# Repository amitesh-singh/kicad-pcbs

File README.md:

### links

sabor awesome shift register boards
* http://repos.borg.ch/projects/pcbs/trunk/shift_regs/doc/shift_regs.sch.svg
* http://repos.borg.ch/projects/pcbs/trunk/shift_regs/doc/shift_regs_bidi.sch.svg
* http://repos.borg.ch/projects/pcbs/trunk/shift_regs/doc/shift_regs_bidi.html

### manifacturer
- oshpark: 6 dollars per 3 board (5cm x 5cm) - prototype service  
   http://docs.oshpark.com/services/
   * i probably order my first board from here.
- https://www.elecrow.com/services/pcb-prototyping.html
-  macrofab https://macrofab.com/
- seedstudio
- dirtypcb : dirtypcb wants *edge.cuts.gm1 into *.gko extension
- lionscircuits: http://www.lioncircuits.com/ -  looks promising for small number for prototypes.

### Enable menu icons
On my home PC, the menu icons were absent in kicad somehow.
running this command fixes those:

$ gsettings set org.gnome.settings-daemon.plugins.xsettings overrides "{'Gtk/ButtonImages': <1>, 'Gtk/MenuImages': <1>}"

### Panelize PCBs
- http://projects.borg.ch/electronics/kicad/panelize.html#A%20Bigger%20Example

- put 2.5-3mm space between each pcb as 1mm space would take up by cutter tool.
#### how to use panelize script
 panelize.py configfile
### Custom PCBs how to
 https://andrehessling.de/2016/09/13/getting-a-custom-board-outline-from-an-svg-file-into-kicad/

### lib and pretty file for ICs
 - https://www.snapeda.com/about/import/

### Kicad setup guide

#### first time setup.  

1. Setting folders for lib,footprints and 3d shapes.

- create a dir named "Kicad" in ~/repos/
- cd Kicad
- git clone https://github.com/KiCad/kicad-library
- git clone https://github.com/KiCad/kicad-packages3D
- git clone https://github.com/KiCad/kicad-footprints
- open Kicad  
   Go to Preferences -> Configure path ->  
   KICAD_PTEMPLATES -> /home/ami/repos/KiCad/kicad-library/template    
   KIGITHUB -> https://github.com/KiCad  
   KISYS3DMOD -> /home/ami/repos/KiCad/kicad-packages3D  
   KISYSMOD -> /home/ami/repos/KiCad/kicad-library/modules  
- open any sch file and do following things  
  Preferences -> component libraries  
  delete all components library files
  click add -> go to /home/ami/repos/KiCad/kicad-library/library and selet all .lib files.  

- open any kicad_pcb files and Preferences -> Footprint libraries manager & delete all the libraries  
  click append with Wizard -> Files on computer -> Next -> /home/ami/repos/KiCad/kicad-footprints and select all the folders

#### setting traces size

PCBNew -> Design rules -> Global design tab

Add track1 - 0.1524  
    track2 - 0.254   
    track3 - 0.381  
    track4 - 0.508
    track5 - 0.8128

    For digital circuits 5v/3.3v, we generally use Track width size 0.381mm

Adding generic Net classes for Power  
Click-> Add -> New Net Class Name -> Power ->  
Clerance -> 0.25  
Track Width -> 0.38  
Via Dia -> 0.4  
Via Drill -> 0.3  
uVia Dia -> 0.3  
uVia Drill -> 0.1  

Go on left side and select Vcc/5v/3.3v/GND and let them use Power Net Class.

Generate good looking PCB artwork from KiCAD 
- https://onetransistor.blogspot.kr/2017/04/kicad-pcb-artwork-display.html?m=1

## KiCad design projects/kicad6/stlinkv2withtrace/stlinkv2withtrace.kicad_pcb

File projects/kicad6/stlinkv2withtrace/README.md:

# make bluepill as stlink

- made this kicad design and it works well 
- refer to this guide 
- https://slemi.info/2018/08/14/making-your-own-st-link-v2/
- https://github.com/skeyzero/stlink_V2/
- already downloaded the hex file in the current folder
On linux,

```
sudo apt install stlink-tools
st-flash --reset --format ihex stlink.hex

```

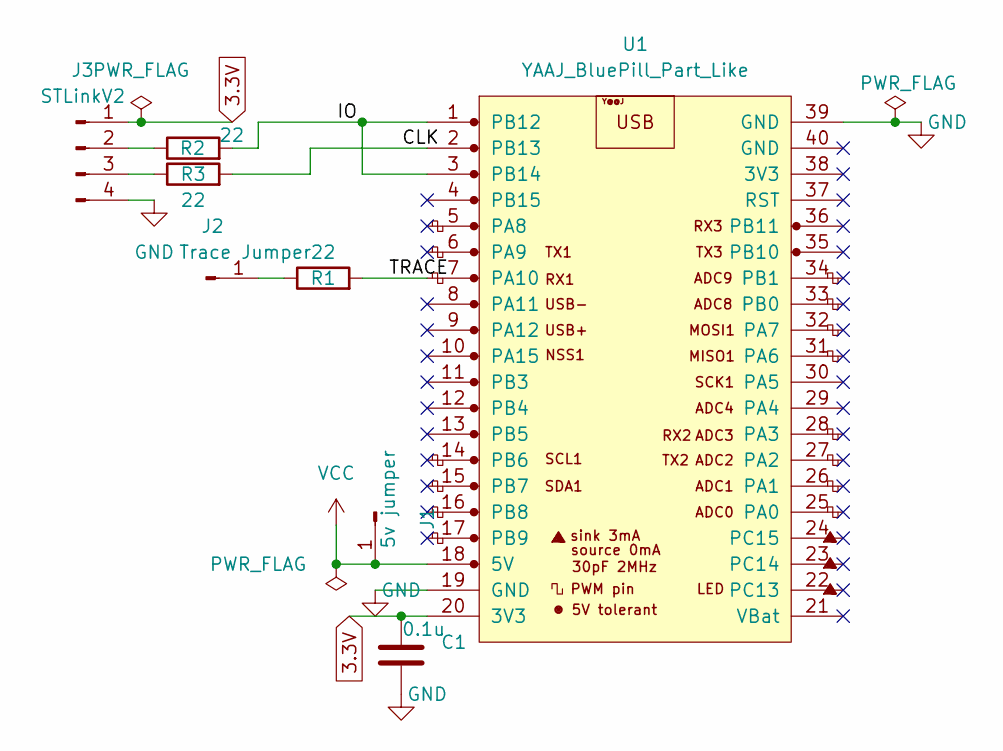
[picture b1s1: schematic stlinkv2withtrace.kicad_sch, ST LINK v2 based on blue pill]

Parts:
C1: 0.1u; C_Axial_L3.8mm_D2.6mm_P7.50mm_Horizontal
J1: 5v jumper; PinSocket_1x01_P2.54mm_Vertical
J2: Trace Jumper; PinSocket_1x01_P2.54mm_Vertical
J3: STLinkV2; PinSocket_1x04_P2.54mm_Horizontal
R1, R2, R3: 22; R_Axial_DIN0207_L6.3mm_D2.5mm_P7.62mm_Horizontal
U1: YAAJ_BluePill_Part_Like; YAAJ_BluePill_2

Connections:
3.3V: C1.1, J3.1, U1.20 (3V3)
/CLK: R3.2, U1.2 (PB13)
/IO: R2.2, U1.1 (PB12), U1.3 (PB14)
/TRACE: R1.2, U1.7 (PA10)
GND: C1.2, J3.4, U1.19 (GND), U1.39 (GND)
unnamed: J2.1, R1.1
unnamed: J3.2, R2.1
unnamed: J3.3, R3.1
VCC: J1.1, U1.18 (5V)

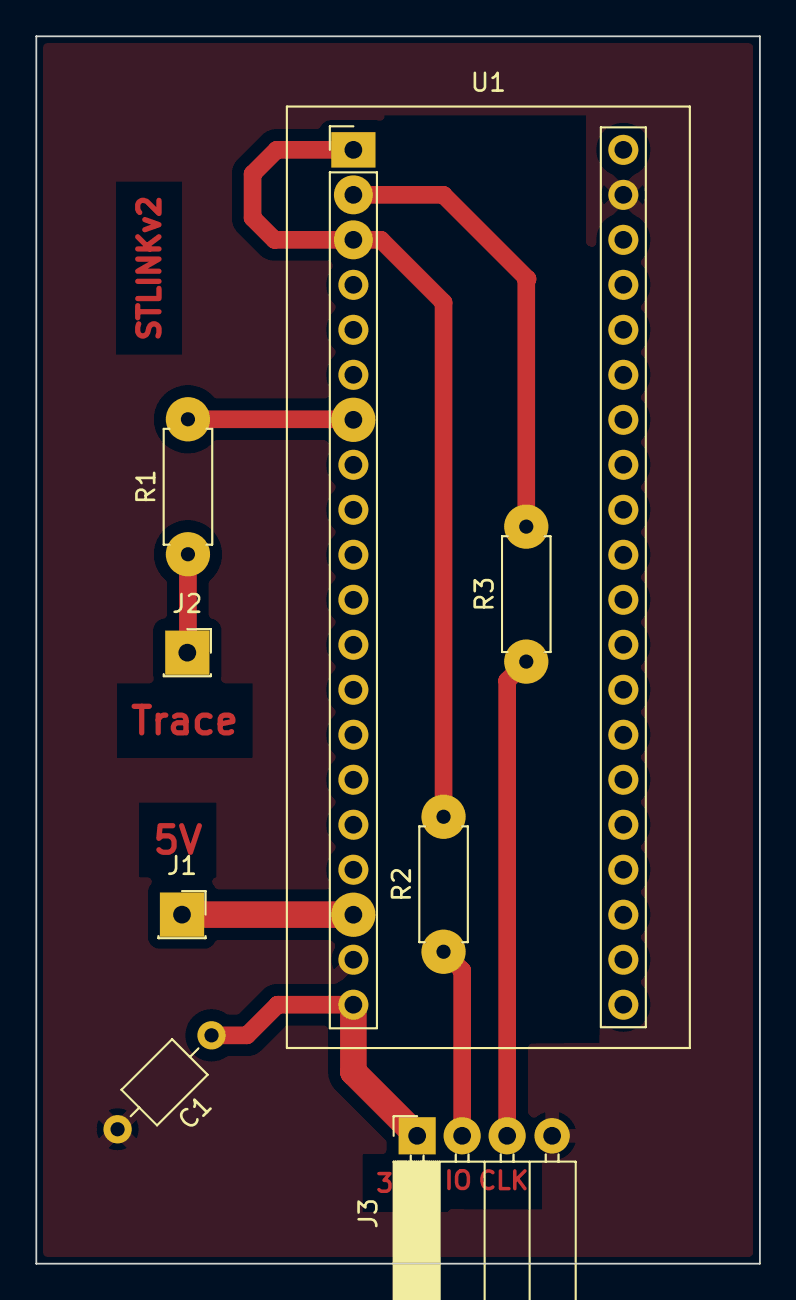
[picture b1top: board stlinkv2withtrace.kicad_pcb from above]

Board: 2 copper layers, 40.9 x 69.3 mm, 8 parts (0 on the bottom side), 9 nets.

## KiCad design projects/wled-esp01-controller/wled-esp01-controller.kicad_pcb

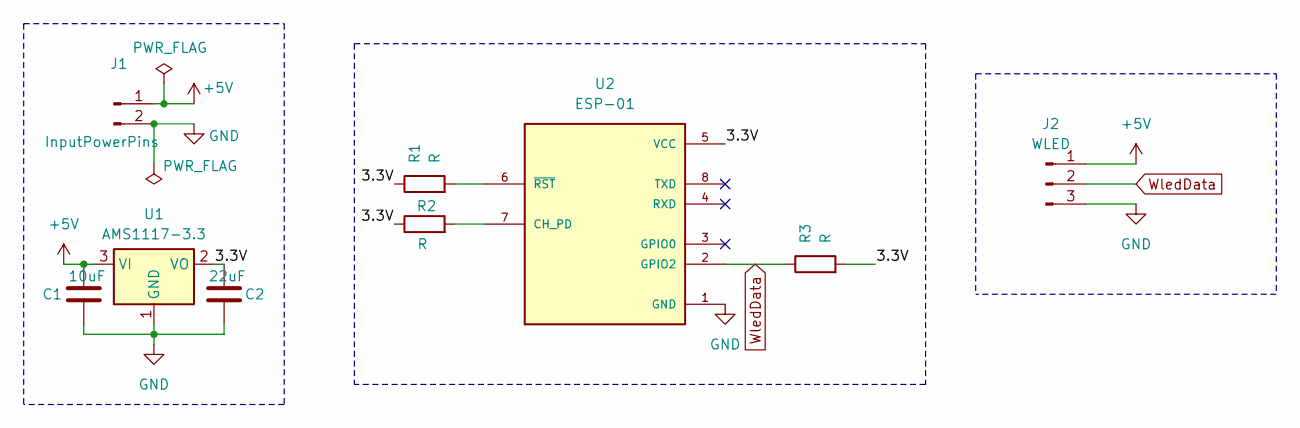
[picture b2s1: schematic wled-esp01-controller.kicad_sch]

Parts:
C1: 10uF; C_Rect_L4.0mm_W2.5mm_P2.50mm
C2: 22uF; C_Rect_L4.0mm_W2.5mm_P2.50mm
J1: InputPowerPins; PinHeader_1x02_P2.54mm_Vertical
J2: WLED; PinHeader_1x03_P2.54mm_Vertical
R1, R2, R3: R; R_0805_2012Metric_Pad1.20x1.40mm_HandSolder
U1: AMS1117-3.3; SOT-223-3_TabPin2
U2: ESP-01; MODULE_ESP-01; PARTREV 1.0

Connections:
+5V: C1.1, J1.1, J2.1, U1.3 (VI)
/3.3V: C2.1, R1.1, R2.1, R3.2, U1.2 (VO), U2.5 (VCC)
GND: C1.2, C2.2, J1.2, J2.3, U1.1 (GND), U2.1 (GND)
unnamed: R2.2, U2.7 (CH_PD)
unnamed: R1.2, U2.6 (~RST)
WledData: J2.2, R3.1, U2.2 (GPIO2)

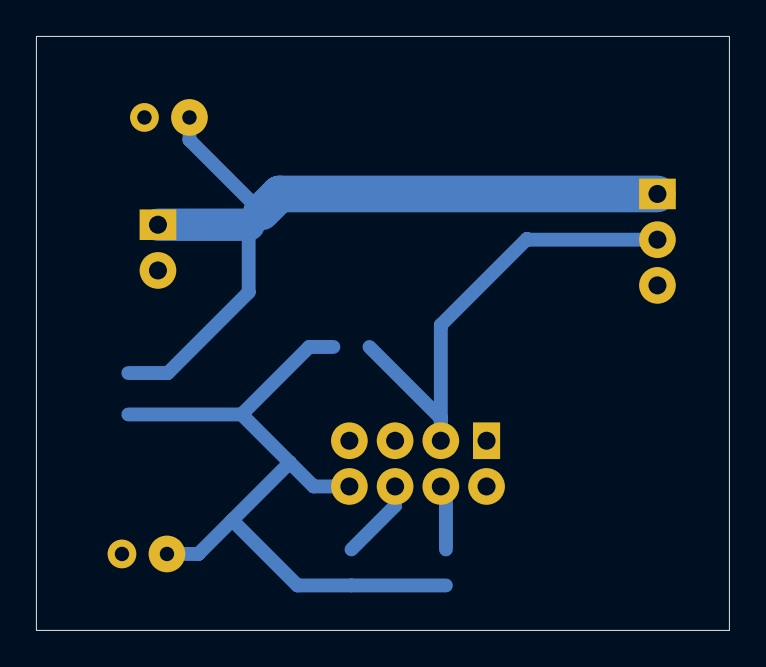
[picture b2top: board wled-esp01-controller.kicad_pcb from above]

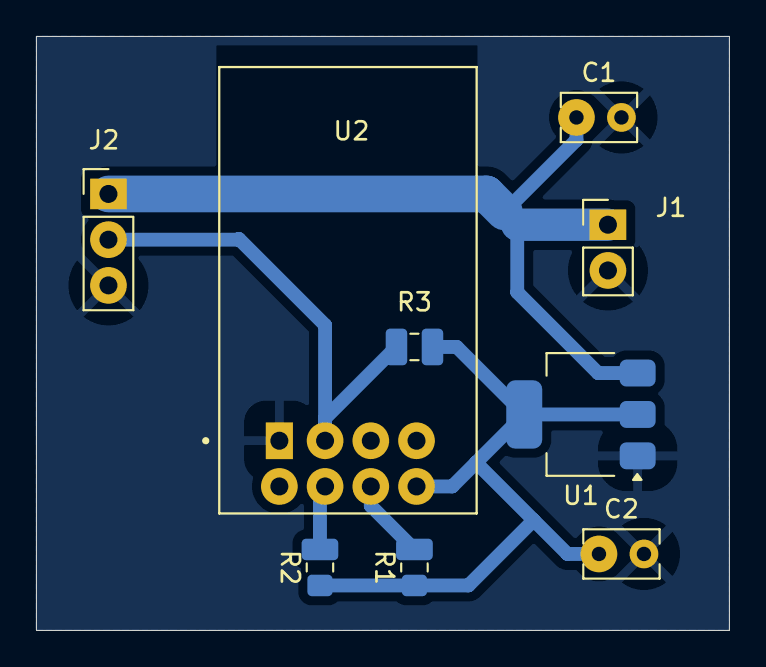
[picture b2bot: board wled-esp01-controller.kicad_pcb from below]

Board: 2 copper layers, 38.5 x 33.0 mm, 9 parts (9 on the bottom side), 6 nets.

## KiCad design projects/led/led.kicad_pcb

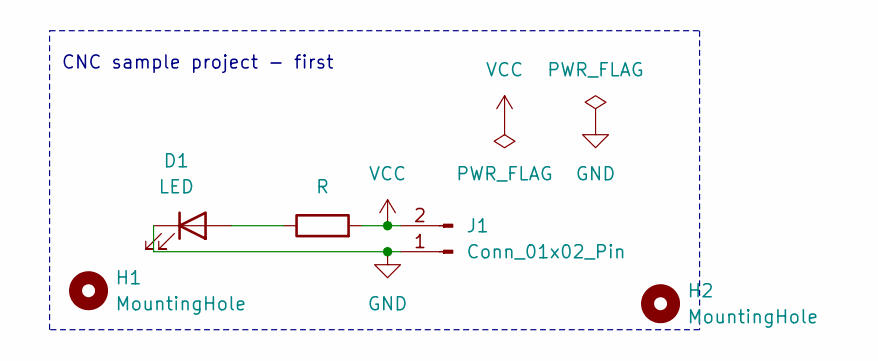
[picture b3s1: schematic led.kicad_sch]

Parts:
D1: LED; LED_0805_2012Metric
H1, H2: MountingHole; MountingHole_2.2mm_M2_DIN965
J1: Conn_01x02_Pin; JST_EH_B2B-EH-A_1x02_P2.50mm_Vertical
R1: R; LED_0805_2012Metric

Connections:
GND: D1.1 (K), J1.1
unnamed: D1.2 (A), R1.1
VCC: J1.2, R1.2

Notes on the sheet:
CNC sample project - first

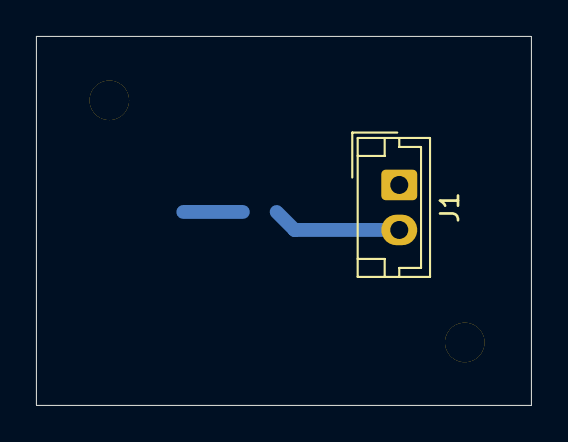
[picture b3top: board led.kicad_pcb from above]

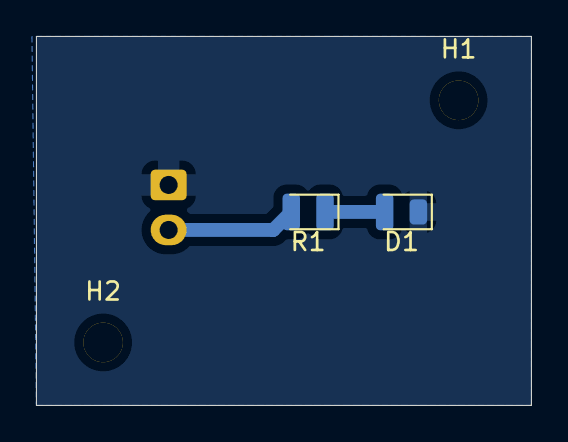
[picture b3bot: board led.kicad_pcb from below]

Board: 2 copper layers, 27.5 x 20.5 mm, 5 parts (4 on the bottom side), 3 nets.

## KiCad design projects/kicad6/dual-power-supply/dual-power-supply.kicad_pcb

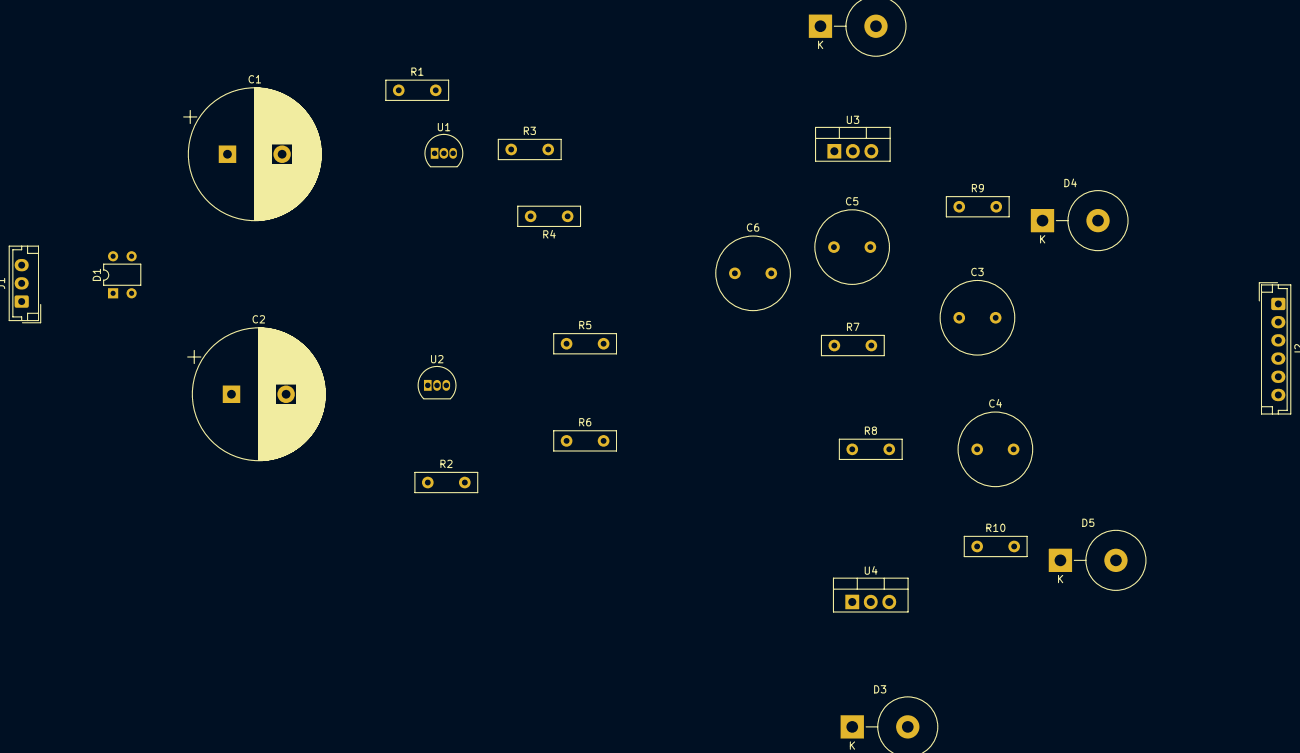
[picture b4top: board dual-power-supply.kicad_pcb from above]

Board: 2 copper layers, 27 parts (0 on the bottom side), 13 nets, no tracks yet.

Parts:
C1, C2: 1000u; CP_Radial_D18.0mm_P7.50mm
C3, C4, C5, C6: 10u; C_Radial_D10.0mm_H12.5mm_P5.00mm
D1: D_Bridge_+-AA; Diode_Bridge_DIP-4_W5.08mm_P2.54mm
D2, D3, D4, D5: D; D_5KPW_P7.62mm_Vertical_KathodeUp
J1: Conn_01x03_Male; JST_EH_B3B-EH-A_1x03_P2.50mm_Vertical
J2: Conn_01x06_Male; JST_EH_B6B-EH-A_1x06_P2.50mm_Vertical
R1, R2: 5k; R_Box_L8.4mm_W2.5mm_P5.08mm
R3, R4, R5, R6: 1k; R_Box_L8.4mm_W2.5mm_P5.08mm
R7, R8: R_Variable; R_Box_L8.4mm_W2.5mm_P5.08mm
R9, R10: R; R_Box_L8.4mm_W2.5mm_P5.08mm
U1, U2: TL431LP; TO-92_Inline
U3: LM317_TO-220; TO-220-3_Vertical
U4: LM337_TO220; TO-220-3_Vertical

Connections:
/AC1: D1.3, J1.1
/AC2: D1.4, J1.3
/V+: C5.1, D2.2 (A), D4.1 (K), J2.1, J2.2, R9.1, U3.2 (VO)
/V+1.25Ref: C4.1, R3.2, R4.1, R8.1
/V-: C6.2, D3.1 (K), D5.2 (A), J2.5, J2.6, R10.2, U4.3 (VO)
/V-1.25Ref: C3.2, R5.2, R6.1, R7.2
GND: C1.2, C2.1, C5.2, C6.1, J1.2, J2.3, J2.4, R4.2, R5.1, U1.2 (A), U2.1 (REF), U2.3 (K)
unnamed: C1.1, D1.1 (+), D2.1 (K), R1.1, U3.3 (VI)
unnamed: C2.2, D1.2 (-), D3.2 (A), R2.2, U4.2 (VI)
unnamed: C3.1, D4.2 (A), R7.1, R9.2, U3.1 (ADJ)
unnamed: C4.2, D5.1 (K), R8.2, R10.1, U4.1 (ADJ)
unnamed: R1.2, R3.1, U1.1 (REF), U1.3 (K)
unnamed: R2.1, R6.2, U2.2 (A)

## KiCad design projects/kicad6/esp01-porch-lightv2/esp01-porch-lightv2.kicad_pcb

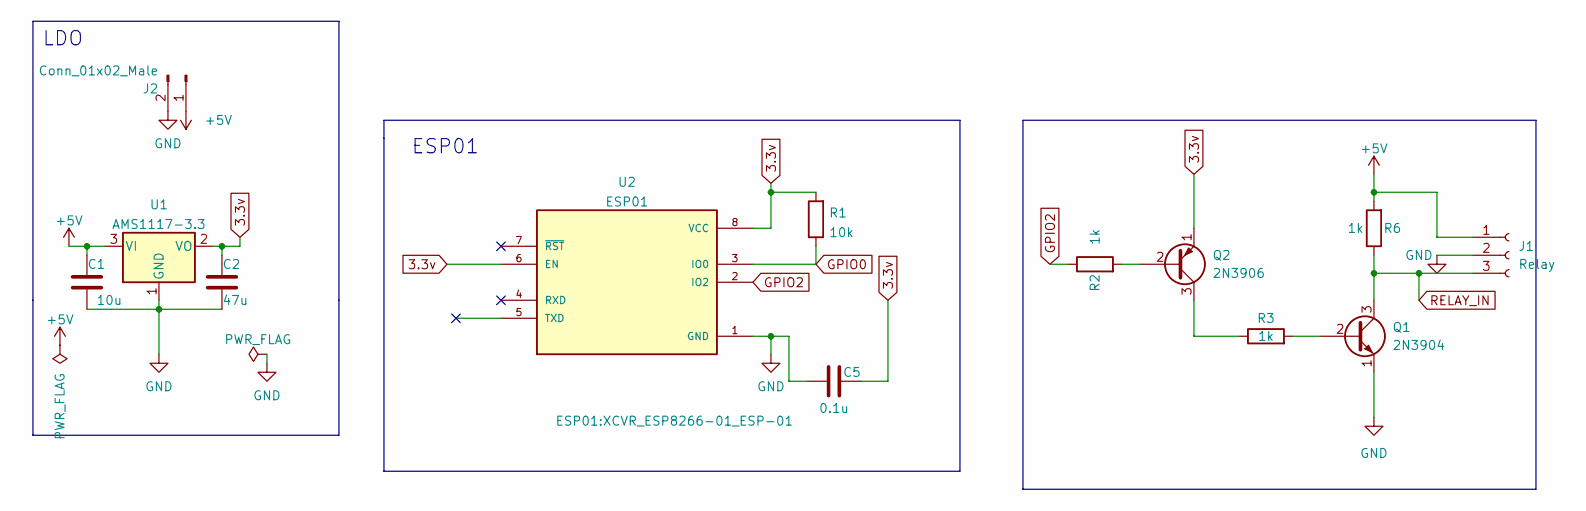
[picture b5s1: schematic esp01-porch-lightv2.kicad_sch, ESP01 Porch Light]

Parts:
C1: 10u; C_0805_2012Metric_Pad1.18x1.45mm_HandSolder
C2: 47u; C_0805_2012Metric_Pad1.18x1.45mm_HandSolder
C5: 0.1u; C_0805_2012Metric_Pad1.18x1.45mm_HandSolder
J1: Relay; PinSocket_1x03_P2.54mm_Vertical
J2: Conn_01x02_Male; PinSocket_1x02_P2.54mm_Vertical
Q1: 2N3904; TO-92_Wide
Q2: 2N3906; TO-92_Wide
R1: 10k; R_0805_2012Metric_Pad1.20x1.40mm_HandSolder
R2, R3, R6: 1k; R_0805_2012Metric_Pad1.20x1.40mm_HandSolder
U1: AMS1117-3.3; SOT-223-3_TabPin2
U2: ESP01; XCVR_ESP8266-01_ESP-01; PARTREV V1.2

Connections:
3.3v: C2.1, C5.1, Q2.1 (E), R1.2, U1.2 (VO), U2.6 (EN), U2.8 (VCC)
+5V: C1.1, J1.1, J2.1, R6.2, U1.3 (VI)
GND: C1.2, C2.2, C5.2, J1.2, J2.2, Q1.1 (E), U1.1 (GND), U2.1 (GND)
GPIO0: R1.1, U2.3 (IO0)
GPIO2: R2.1, U2.2 (IO2)
unnamed: Q1.2 (B), R3.2
unnamed: Q2.2 (B), R2.2
unnamed: Q2.3 (C), R3.1
RELAY_IN: J1.3, Q1.3 (C), R6.1

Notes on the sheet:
ESP01
LDO

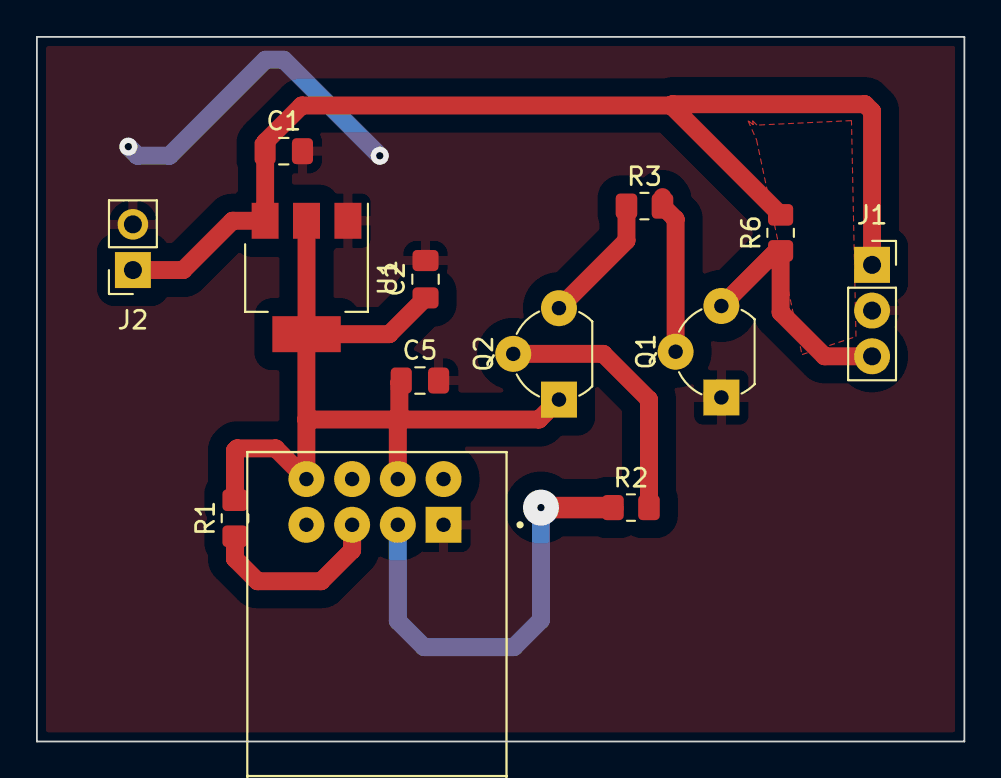
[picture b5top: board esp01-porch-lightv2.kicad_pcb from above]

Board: 2 copper layers, 51.5 x 39.1 mm, 13 parts (0 on the bottom side), 9 nets.

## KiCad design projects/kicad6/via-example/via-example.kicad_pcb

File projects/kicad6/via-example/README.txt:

Use this via example for making jumper wire enabled
single layer board for etching at home.

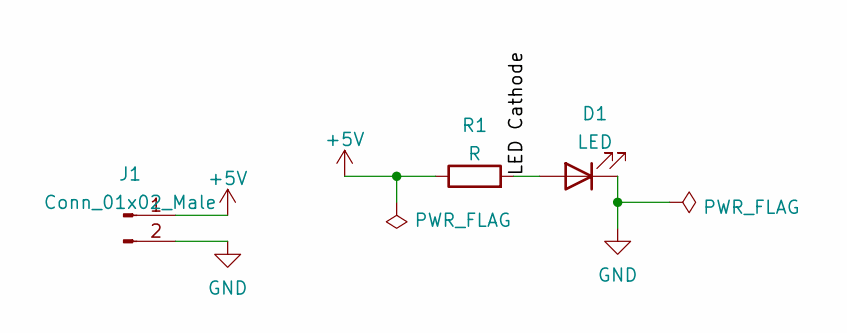
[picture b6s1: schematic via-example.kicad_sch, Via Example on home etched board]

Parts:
D1: LED; LED_0805_2012Metric_Pad1.15x1.40mm_HandSolder
J1: Conn_01x02_Male; PinSocket_1x02_P2.54mm_Vertical
R1: R; R_0805_2012Metric_Pad1.20x1.40mm_HandSolder

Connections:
+5V: J1.1, R1.1
/LED Cathode: D1.2 (A), R1.2
GND: D1.1 (K), J1.2

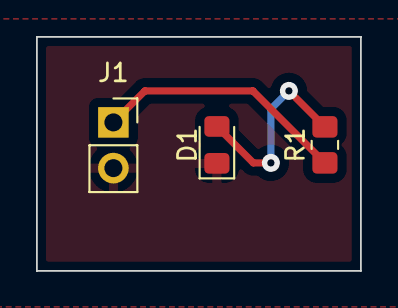
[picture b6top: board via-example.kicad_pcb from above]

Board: 2 copper layers, 18.0 x 13.0 mm, 3 parts (0 on the bottom side), 3 nets.

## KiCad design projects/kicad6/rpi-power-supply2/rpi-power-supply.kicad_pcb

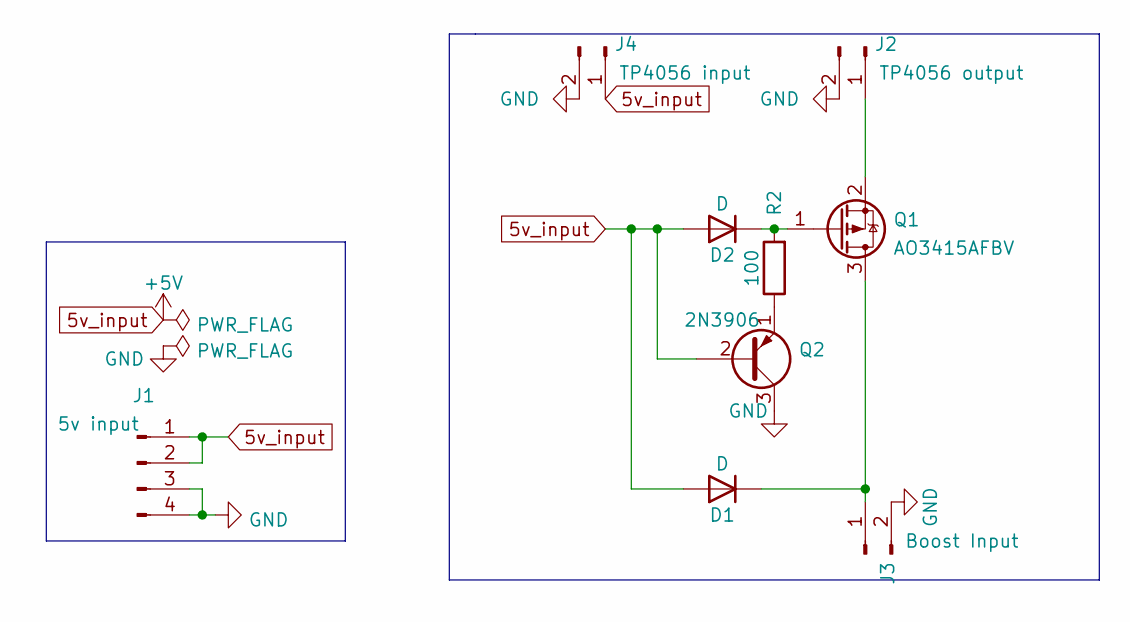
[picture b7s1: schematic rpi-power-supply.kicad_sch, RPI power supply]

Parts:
D1, D2: D; D_3220_8050Metric_Pad2.65x5.15mm_HandSolder
J1: 5v input; PinHeader_1x04_P2.54mm_Vertical_ETCH
J2: TP4056 output; PinSocket_1x02_P2.54mm_Vertical_ETCH
J3: Boost Input; PinSocket_1x02_P2.54mm_Vertical_ETCH
J4: TP4056 input; PinSocket_1x02_P2.54mm_Vertical_ETCH
Q1: AO3415AFBV; SOT-23_Handsoldering
Q2: 2N3906; TO-92_HandSolder
R2: 100; R_0805_2012Metric_Pad1.20x1.40mm_HandSolder

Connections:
5v_input: D1.2 (A), D2.2 (A), J1.1, J1.2, J4.1, Q2.2 (B)
GND: J1.3, J1.4, J2.2, J3.2, J4.2, Q2.3 (C)
unnamed: D2.1 (K), Q1.1 (G), R2.2
unnamed: J2.1, Q1.2 (S)
unnamed: D1.1 (K), J3.1, Q1.3 (D)
unnamed: Q2.1 (E), R2.1

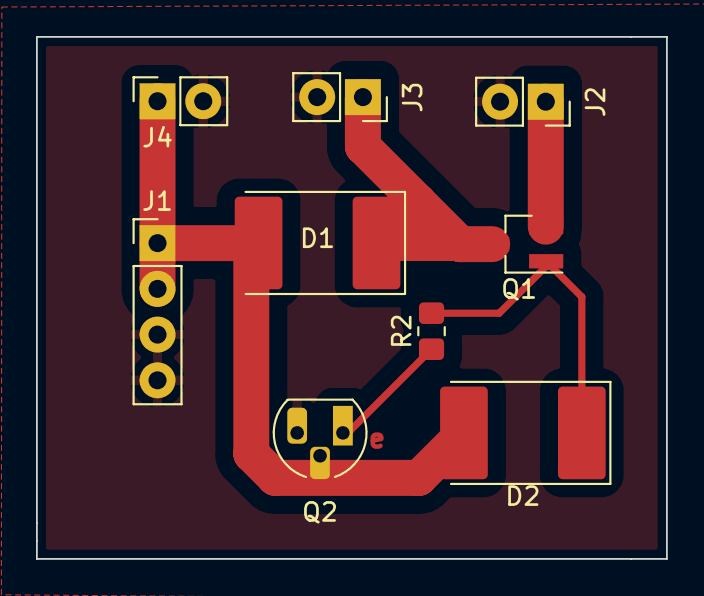
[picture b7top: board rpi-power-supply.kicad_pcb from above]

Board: 2 copper layers, 35.0 x 29.0 mm, 9 parts (0 on the bottom side), 6 nets.

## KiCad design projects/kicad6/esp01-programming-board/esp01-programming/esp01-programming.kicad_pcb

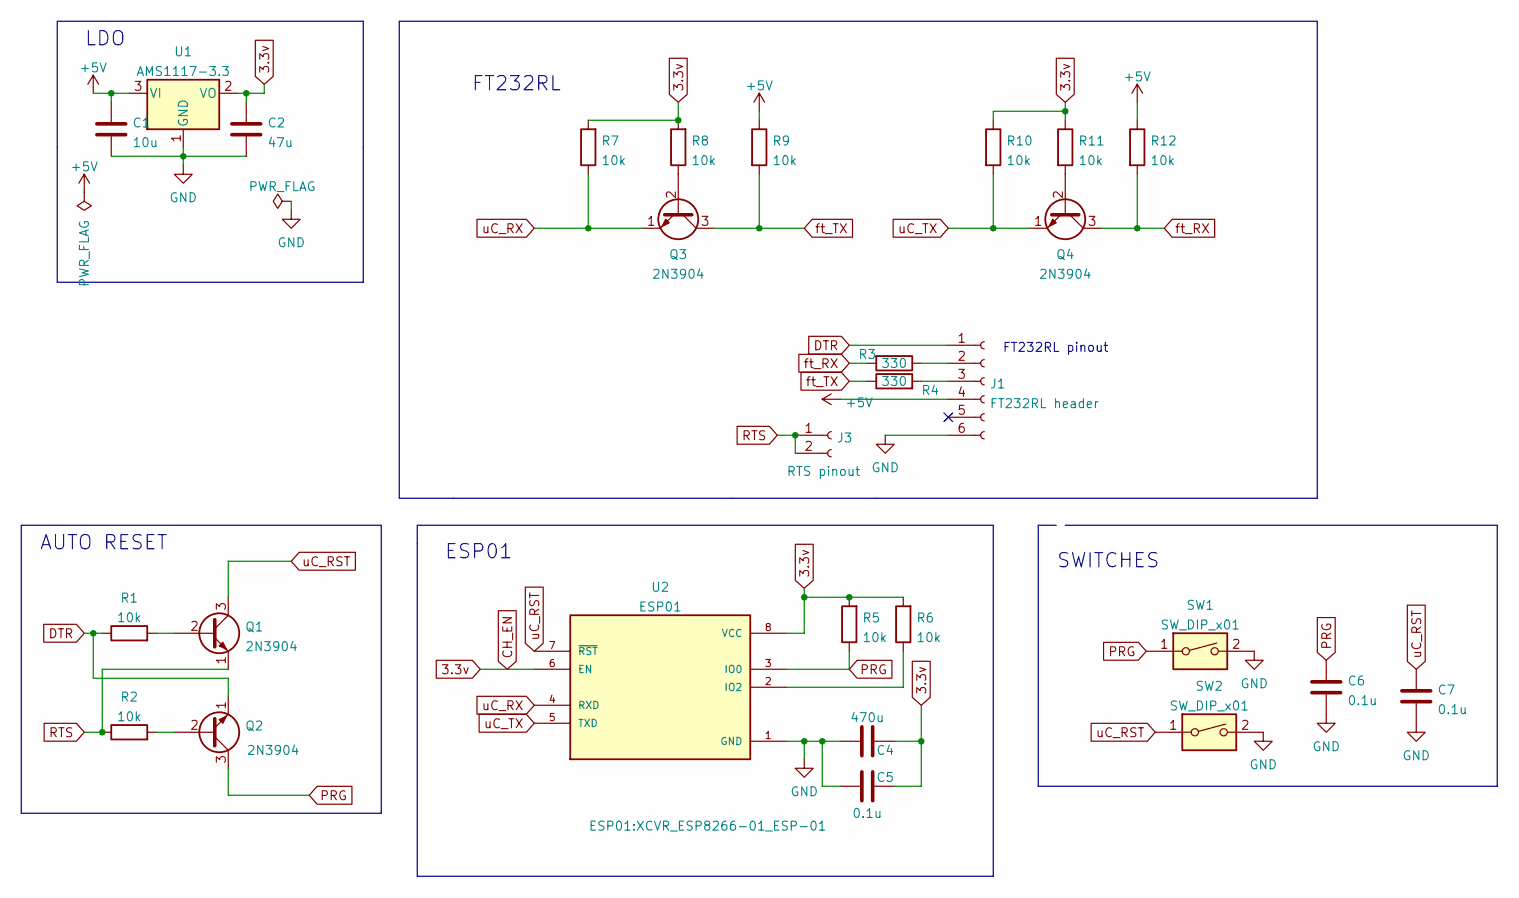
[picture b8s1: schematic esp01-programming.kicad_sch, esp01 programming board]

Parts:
C1: 10u; C_0805_2012Metric_Pad1.18x1.45mm_HandSolder
C2: 47u; C_0805_2012Metric_Pad1.18x1.45mm_HandSolder
C4: 470u; C_Radial_D4.0mm_H7.0mm_P1.50mm
C5, C6, C7: 0.1u; C_0805_2012Metric_Pad1.18x1.45mm_HandSolder
J1: FT232RL header; PinHeader_1x06_P2.54mm_Vertical
J3: RTS pinout; PinSocket_1x02_P2.54mm_Vertical_ETCH
Q1, Q2, Q3, Q4: 2N3904; TO-92_Wide
R1, R2, R5, R6, R7, R8, R9, R10, R11, R12: 10k; R_0805_2012Metric_Pad1.20x1.40mm_HandSolder
R3, R4: 330; R_0805_2012Metric_Pad1.20x1.40mm_HandSolder
SW1, SW2: SW_DIP_x01; SW_PUSH_6mm_H5mm
U1: AMS1117-3.3; SOT-223-3_TabPin2
U2: ESP01; XCVR_ESP8266-01_ESP-01; PARTREV V1.2

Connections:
3.3v: C2.1, C4.1, C5.1, R5.2, R6.2, R7.2, R8.2, R10.1, R11.1, U1.2 (VO), U2.6 (EN), U2.8 (VCC)
+5V: C1.1, J1.4, R9.1, R12.1, U1.3 (VI)
DTR: J1.1, Q2.1 (E), R1.1
GND: C1.2, C2.2, C4.2, C5.2, C6.2, C7.1, J1.6, SW1.2, SW2.2, U1.1 (GND), U2.1 (GND)
unnamed: J1.2, R3.1
unnamed: J1.3, R4.2
unnamed: Q1.2 (B), R1.2
unnamed: Q2.2 (B), R2.2
unnamed: Q3.2 (B), R8.1
unnamed: Q4.2 (B), R11.2
unnamed: R6.1, U2.2 (IO2)
PRG: C6.1, Q2.3 (C), R5.1, SW1.1, U2.3 (IO0)
RTS: J3.1, J3.2, Q1.1 (E), R2.1
ft_RX: Q4.3 (C), R3.2, R12.2
ft_TX: Q3.3 (C), R4.1, R9.2
uC_RST: C7.2, Q1.3 (C), SW2.1, U2.7 (~RST)
uC_RX: Q3.1 (E), R7.1, U2.4 (RXD)
uC_TX: Q4.1 (E), R10.2, U2.5 (TXD)

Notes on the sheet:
SWITCHES
LDO
ESP01
FT232RL
AUTO RESET
FT232RL pinout

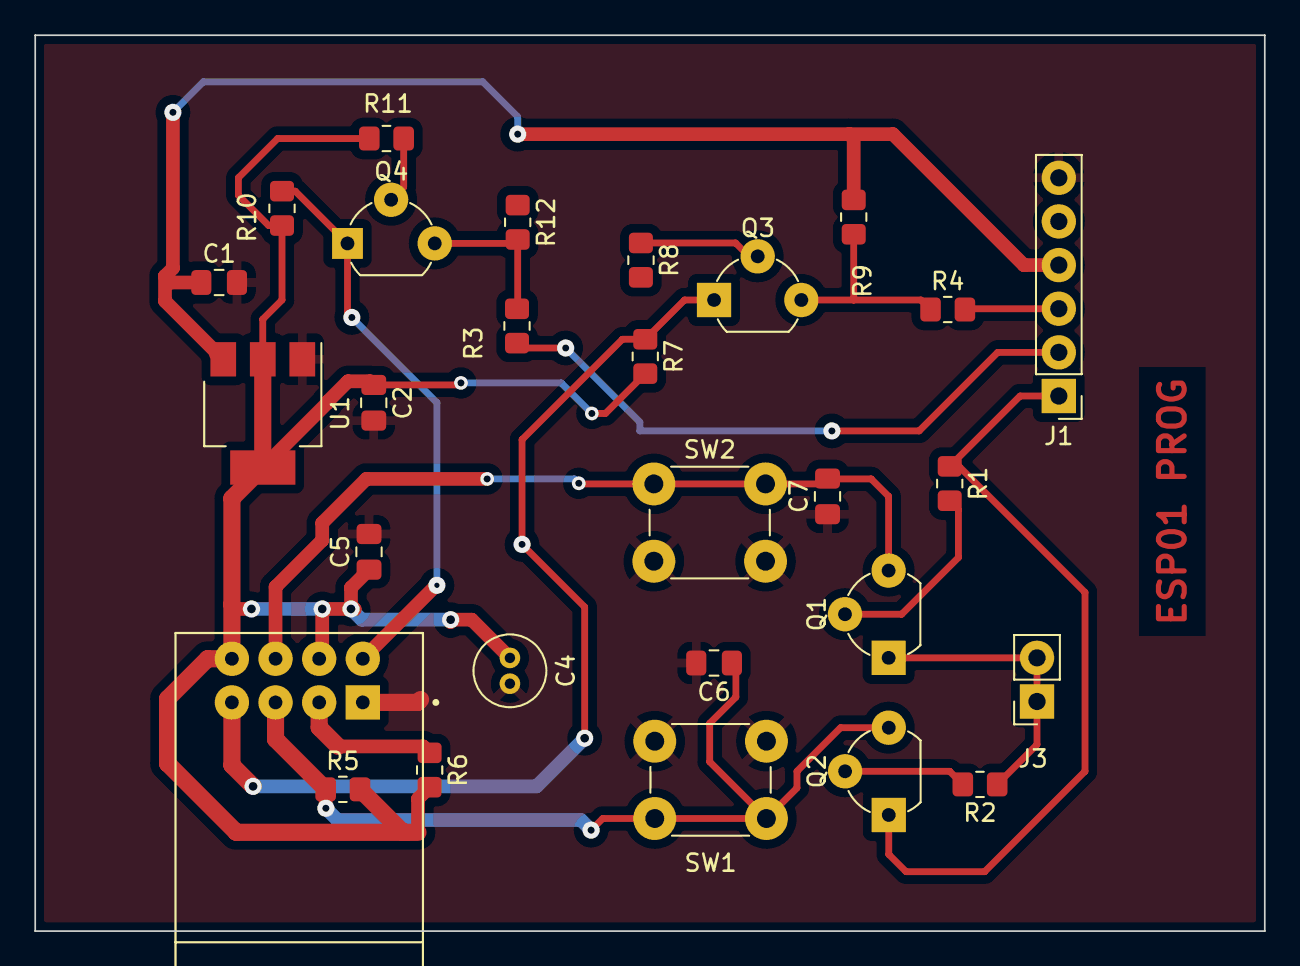
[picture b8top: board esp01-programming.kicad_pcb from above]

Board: 2 copper layers, 71.6 x 52.1 mm, 28 parts (0 on the bottom side), 18 nets.

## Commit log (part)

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2016-09-04 Add atmega16 schematics and fritzing file.
2016-09-10 Add new parts
2016-10-02 led sketch added
2016-10-12 Add new designs
2016-10-23 Add led example for kicad.
2016-10-29 Add ST7735 breakout TFT display
2016-10-29 Add ST7735 connections with AVR atmega16a
2017-01-18 Add README
2017-01-23 Add 74hc595 sch with attiny85
2017-01-26 Add nRF24 breakout board
2017-01-26 Add nRF24 v0.2
2017-01-26 Add final nRF24 board - production ready
2017-01-27 add 7 segment schematic
2017-01-28 Add led2layer example
    - a minimal example which shows how to make
    2 layer PCB. also shows how to place a component on
    back side of pcb.
    - added a cool logo of mine on that board.
2017-01-28 Add info abt manufacturers
2017-01-28 Add a nice logo
2017-01-28 Add attiny13a schematic
2017-01-29 Add sabor panelize tool.
2017-01-29 Add new led pro
2017-01-29 Add atiny13 full schematic/pcb
2017-01-29 make a better pcb
    included sabor suggestions
    1. Change vcc copper fill to GND fill
    2. remove gnd traces
    3. redraw vcc traces
    4. move bypass capacitor close to Vcc/GND as much as possible.
2017-01-29 remove bak files
    remove backup files
2017-01-29 Add gitignore
    Add bak files
2017-01-29 change name to ISP
2017-01-29 make vcc track size bigger
2017-01-29 make vcc track size bigger
    and also add logo of board.
2017-01-29 Add sabor common libraries
2017-01-29 Add attony13a
2017-01-29 Add capacitor across switch
2017-01-29 Add 6mm switch button
2017-01-29 Add attiny13a
2017-01-29 move the headers a bit
2017-01-29 Add production ready code
2017-02-01 use latest panelize script by sabor
2017-02-01 Add panilized kicad pcb and config file
    usage:
    panelize.py config file
2017-02-01 remove gerber files
2017-02-01 make it better.
2017-02-01 Add round shape board example
2017-02-01 Add config file for panelize.
    it seems that panelize won;t work with round leds.
2017-02-02 update the 7segment a bit
    mistakes corrected.
    - remove right angled traces
    - minimize the vias
    - add a 2.0 mm hole
2017-02-02 round leds: Add one more GND plane
2017-02-02 Add Kitchen timer schematic
    add sabor digital library as well.
2017-02-02 Associate components
2017-02-02 fix the switch circuit.
2017-02-02 fix circuit for 7 segment display.
2017-11-05 make it compatible with kicad recent version
2017-11-09 kicad: add new schematic/pcb for ams1117 3.3v
2017-11-09 kicad: breadboad - add generic board skeleton
    Work in progress.
2017-11-10 breadboard: Add esp12e into board
2017-11-10 AMS1117: Add way to thermal vias
    This is based on https://www.youtube.com/watch?v=Hp5ngKtl7S4
2017-11-10 multisheet: Add multisheet example in kicad.
    This makes design look good.
2017-11-10 remove old projects
2017-11-12 breadboard: Add bboard-3rows component
2017-11-12 breadboard: make the pins type to passive.
2017-11-12 breadboard: esp12e - work is almost completed.
2017-11-12 Add gitignore
2017-11-12 Revert "Add gitignore"
    This reverts commit 1d0808174f2c1fbc4e2cf73c68065f4eadfb9096.
2017-11-12 fix sch
2017-11-13 library: Add AMS1117-3.3 lib
2017-11-13 breadboard: modify the libraries path
2017-11-13 update README.md
    Add on how to setup kicad for first time.
2017-11-13 Add latest
2017-11-13 README.md - add abt how to add track width options
2017-11-13 breadboard: add net class power
2017-11-14 breadboard: fix the mistakes in esp12e board design
2017-11-14 multisheet: Add stm32 sch imported from another project.
2017-11-14 Add multipower schematic.
2017-11-14 gitignore update
2017-11-15 Add docs abt heirarchical sheet
2020-09-28 rename the folder.
2020-10-16 update the panelize tool
2022-02-19 Add esp01 board - not finished
2022-02-28 Add rpi power supply schematic.
2022-03-04 Add via example for home etched boards
2022-03-05 Add local footprints and symbols
2022-03-12 Add esp01 porch light pcb
2022-03-12 Add esp01 adapter pcb
2022-03-12 Add MIC5209 symbol/footprint
2022-03-12 Add new changes
2022-03-12 Add new footprints
2022-03-14 esp01_porch light: fix the GNDing
2022-03-15 Add porch light updated schematic
2022-03-19 add v2 of porch light
2022-03-19 update esp 01 port light PCB
2022-03-19 esp porch ligh v2: finished
2022-04-15 Add dual power supply kicad
2022-05-08 Add doorsensor v2 version with reed switch
2022-05-15 Add stlinkv2
2022-05-17 Add stlink v2 diy programmer
2023-12-22 Add pin header 1x10 etch friendly
2023-12-31 Add new files
2023-12-31 freecad/learning sample: add a sample
2024-01-01 freecad readme
2024-01-03 Add more freecad designs
2024-01-03 Add Gear readme
2024-01-03 freecad: trim edge example
2024-01-03 freecad: Add gear and mirror examples
2024-01-04 freecad: Add text example
2024-01-06 Add more freeCad projects
2024-01-07 freeCAD: add angled hole example
2024-01-07 freeCad: add cool projects
2024-01-15 freeCAD: add car mobile holder leg
    This fixes my car mobile holder
2024-01-15 freecad: Add glass
2024-01-16 animation example
2024-01-16 add more animation
2024-01-25 add new code
2024-01-26 Add more files
2024-01-29 Add more
2024-01-29 freeCAD: final project
2024-02-01 Add best design for making box
2024-02-01 Add reamde
2024-02-03 freeCAD: add new projects
2024-02-04 Add PCB shaker project desc
2024-02-04 Adafruit design - reverse engineering
2024-02-05 Add boolean op example
2024-02-06 freeCAD: add extension drawing
2024-02-07 freeCAD: add new designs
2024-02-08 freeCAD: add more projects
2024-02-09 Add printerRefillBottle Cap example
2024-02-11 Add config table example
2024-02-23 freecad: Add springs example
2024-03-05 Add spoon
2024-03-28 Add snap-fit example
2024-04-03 add snap-fit box example
2024-04-21 Add usb boost power supply
    XY-016 2A DC-DC Step Up 5V/9V/12V/28V Power Module with Micro USB
2024-04-26 add thickness example
2024-11-29 freecad: add dice example
2024-11-30 Add updated one
2024-12-31 Add jumper wire organizer
2025-01-31 Add latest freecad stuffs
2025-01-31 add door stopper
2025-02-02 Add guide
2025-02-14 Add the uno box enclosure
2025-04-28 Add README.md
2025-05-20 Add kitchen cover gap filler
2025-05-20 Add all
2025-05-24 add usb cable organizer
2025-05-28 Add suitcase
2025-05-28 Add more designs
2025-05-31 add hanger mod
2025-08-02 Add new models
2025-08-19 Add new stuff
2025-08-25 Add air-pump design
2025-09-22 add rigol hook cover
2025-12-26 Add design for Anolex 3030 Evo Max Fixture
2025-12-28 Add new led project example for pcb milling
2025-12-29 update millproject
2025-12-30 Add template for cnc based kicad projects
2026-01-01 push
2026-01-13 add toilet cover pad design
2026-01-18 add rpi-wifi
2026-01-18 Add documents about Freecad kicad
2026-01-24 Add assembly workbench
2026-02-03 Add milkbasket logo
2026-02-07 Add avi bottle design
2026-02-07 add aarav-table hook
2026-02-09 Add bits tool box nice cover
2026-03-13 Add rpi2 enclosure design
2026-04-04 Add all freecad stuff
